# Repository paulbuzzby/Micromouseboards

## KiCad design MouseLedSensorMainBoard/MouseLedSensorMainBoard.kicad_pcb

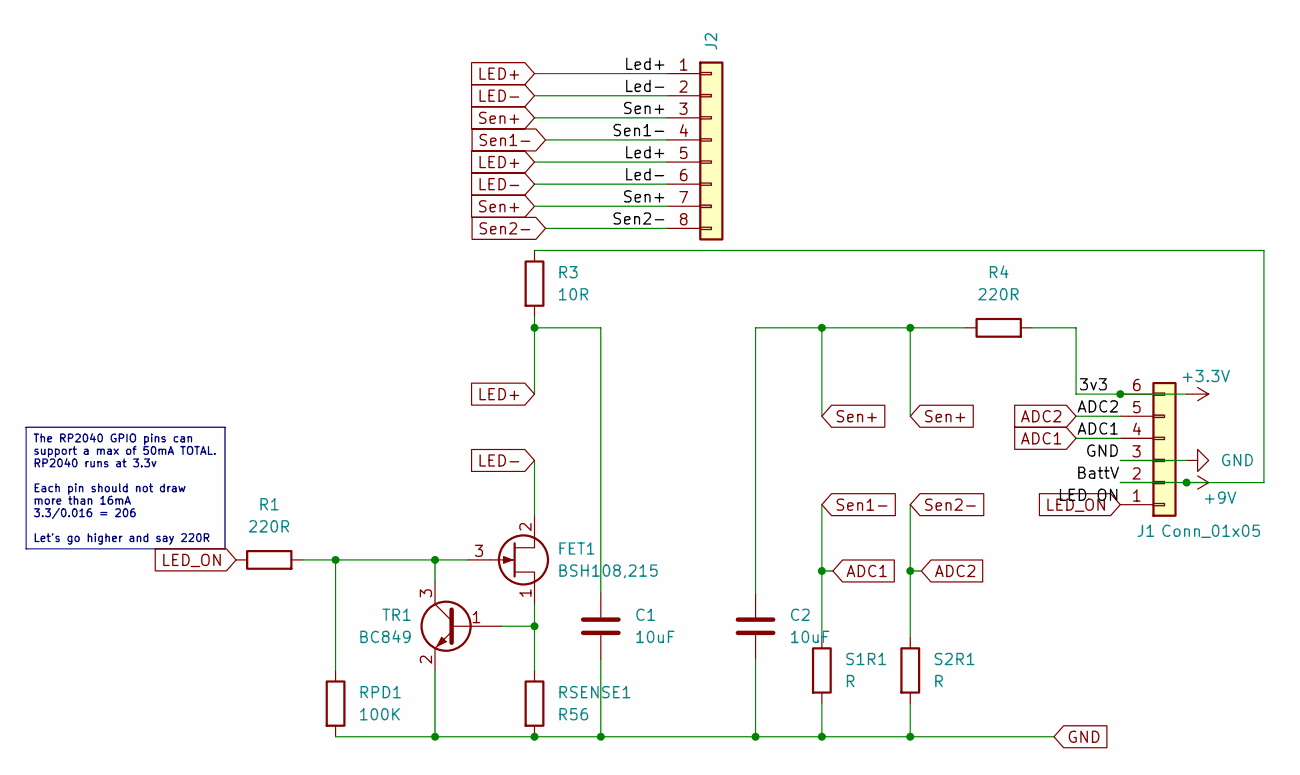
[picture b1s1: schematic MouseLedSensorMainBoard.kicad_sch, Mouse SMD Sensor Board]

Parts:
C1, C2: 10uF; C_0805_2012Metric_Pad1.18x1.45mm_HandSolder
FET1: BSH108,215; SOT-23
J1: Conn_01x05; PinHeader_1x06_P2.54mm_Vertical
J2: Conn_01x08; PinHeader_1x08_P2.54mm_Vertical
R1, R4: 220R; R_0805_2012Metric_Pad1.20x1.40mm_HandSolder
R3: 10R; R_0805_2012Metric_Pad1.20x1.40mm_HandSolder
RPD1: 100K; R_0805_2012Metric_Pad1.20x1.40mm_HandSolder
RSENSE1: R56; R_0805_2012Metric_Pad1.20x1.40mm_HandSolder
S1R1, S2R1: R; R_0805_2012Metric_Pad1.20x1.40mm_HandSolder
TR1: BC849; SOT-23

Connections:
+3.3V: J1.6, R4.2
+9V: J1.2, R3.1
ADC1: J1.4, J2.4, S1R1.1
ADC2: J1.5, J2.8, S2R1.1
GND: C1.2, C2.2, J1.3, RPD1.2, RSENSE1.2, S1R1.2, S2R1.2, TR1.2 (E)
LED+: C1.1, J2.1, J2.5, R3.2
LED-: FET1.2 (D), J2.2, J2.6
LED_ON: J1.1, R1.1
unnamed: FET1.3 (G), R1.2, RPD1.1, TR1.3 (C)
unnamed: FET1.1 (S), RSENSE1.1, TR1.1 (B)
Sen+: C2.1, J2.3, J2.7, R4.1

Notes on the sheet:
The RP2040 GPIO pins can support a max of 50mA TOTAL. RP2040 runs at 3.3v Each pin should not draw more than 16mA 3.3/0.016 = 206 Let's go higher and say 220R

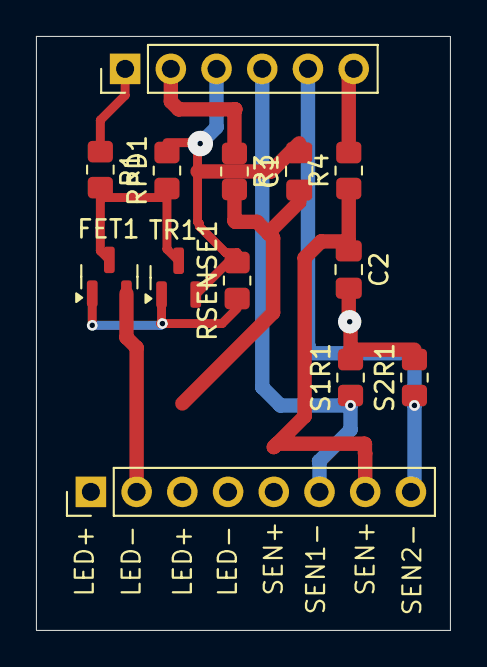
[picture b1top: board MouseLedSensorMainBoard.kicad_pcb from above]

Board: 2 copper layers, 23.0 x 33.0 mm, 13 parts (0 on the bottom side), 11 nets.

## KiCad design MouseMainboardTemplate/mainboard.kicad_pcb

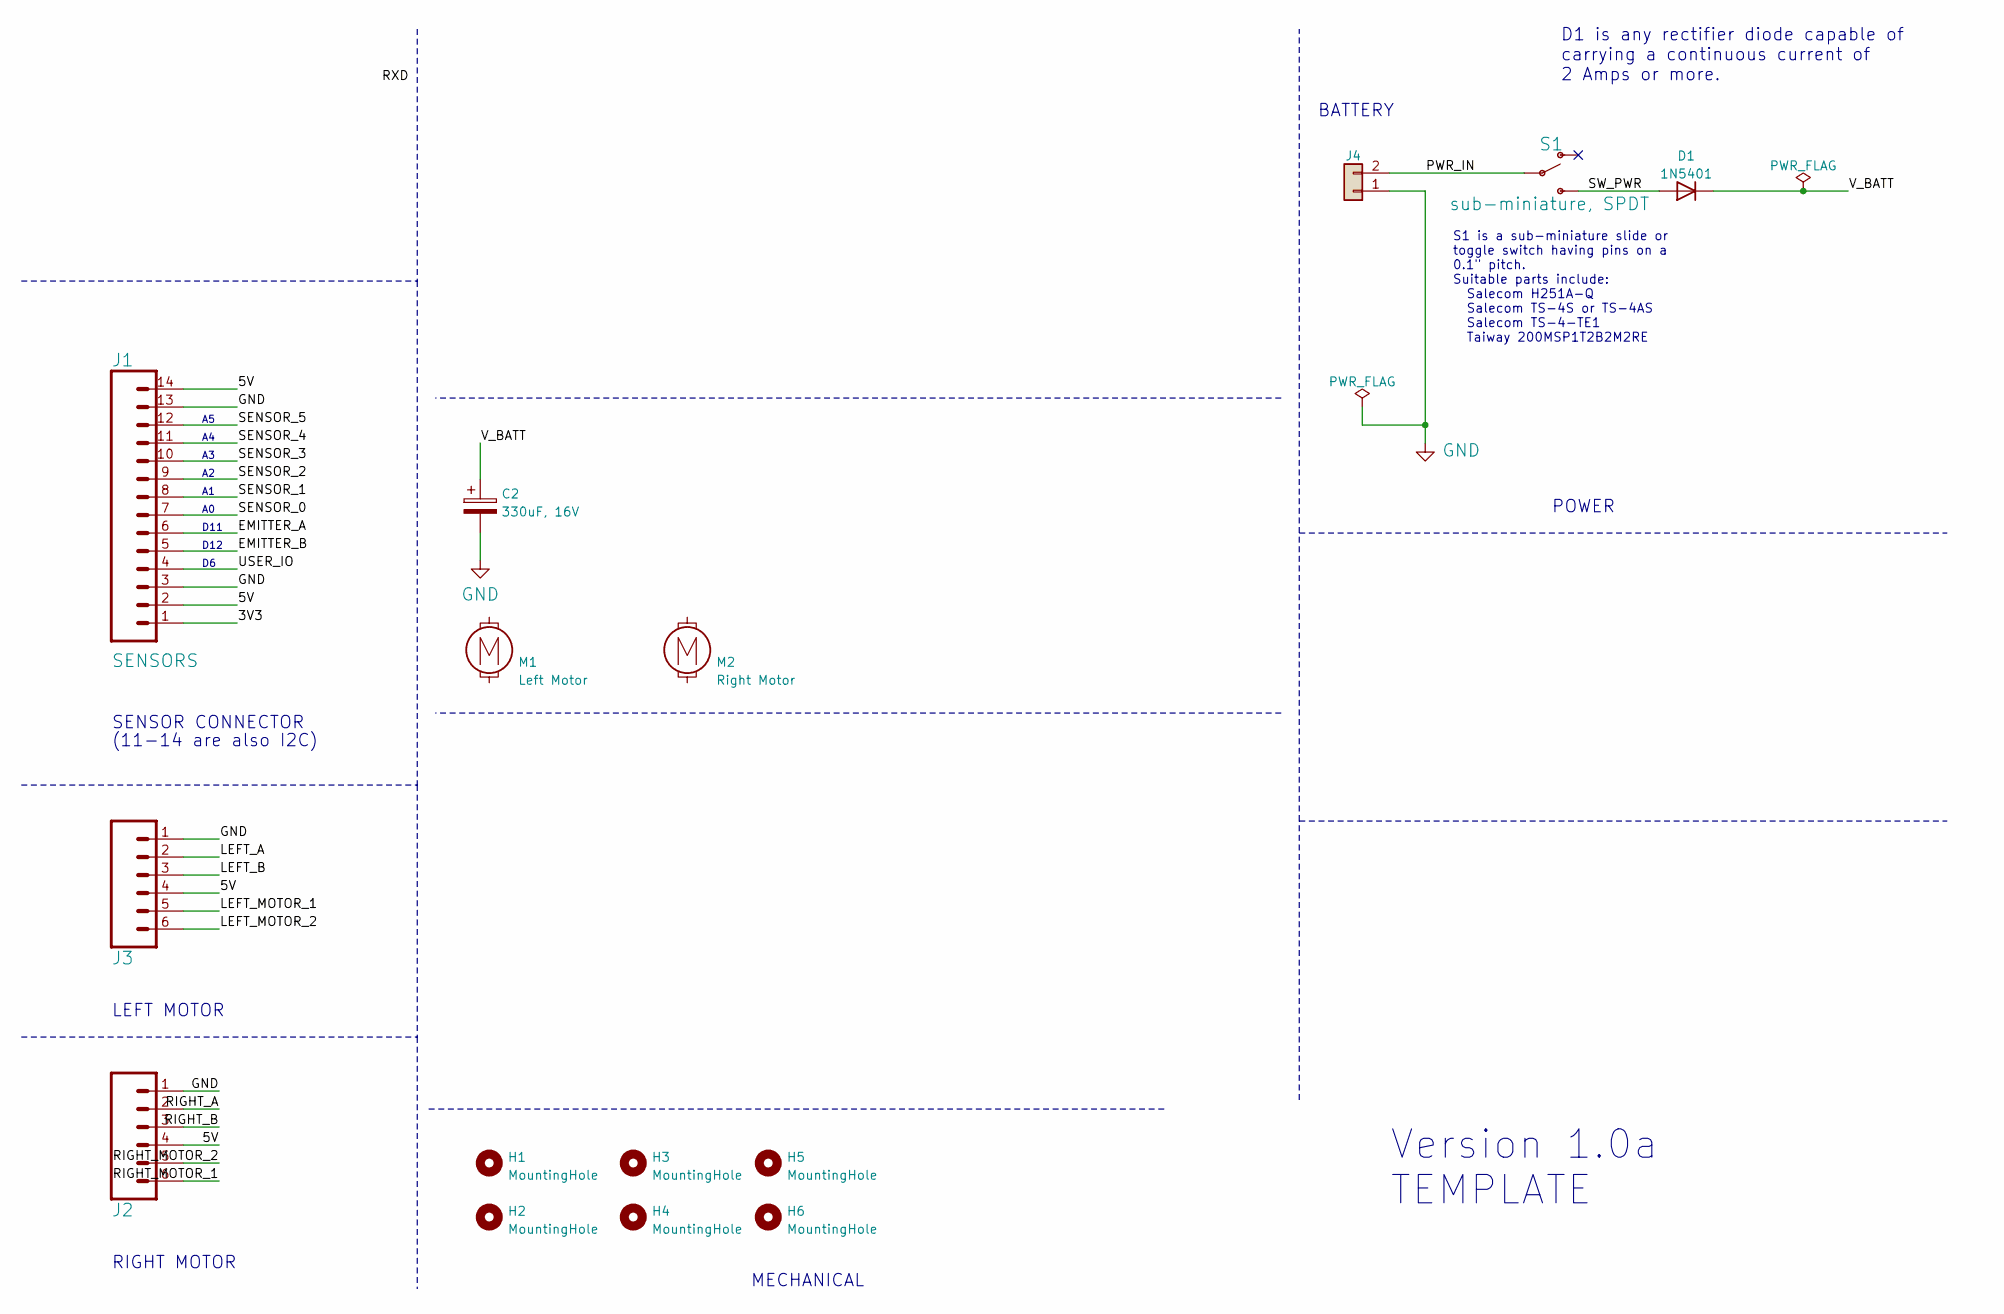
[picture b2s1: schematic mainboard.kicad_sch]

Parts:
C2: 330uF, 16V; CP_Radial_D8.0mm_P2.50mm
D1: 1N5401; D_DO-201AD_P15.24mm_Horizontal
H1, H2, H3, H4, H5, H6: MountingHole; MountingHole_3.2mm_M3_clearance
J1: SENSORS; 1X14_LOCK_LONGPADS
J2, J3: CONN_06SILK_FEMALE_PTH; 1X06_LOCK_LONGPADS
J4: POWER; Molex_KK-254_AE-6410-02A_1x02_P2.54mm_Vertical
M1: Left Motor; MINI-METAL-GEARMOTOR-WITH-BRACKET
M2: Right Motor; MINI-METAL-GEARMOTOR-WITH-BRACKET
S1: sub-miniature, SPDT; SW_MINI-SPDT-RTECH-78-0564

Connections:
/3V3: J1.1
/5V: J1.2, J1.14, J2.4, J3.4
/EMITTER_A: J1.6
/EMITTER_B: J1.5
/LEFT_A: J3.2
/LEFT_B: J3.3
/LEFT_MOTOR_1: J3.5
/LEFT_MOTOR_2: J3.6
/PWR_IN: J4.2, S1.2
/RIGHT_A: J2.2
/RIGHT_B: J2.3
/RIGHT_MOTOR_1: J2.6
/RIGHT_MOTOR_2: J2.5
/SENSOR_0: J1.7
/SENSOR_1: J1.8
/SENSOR_2: J1.9
/SENSOR_3: J1.10
/SENSOR_4: J1.11
/SENSOR_5: J1.12
/SW_PWR: D1.2 (A), S1.3 (S)
/USER_IO: J1.4
/V_BATT: C2.1, D1.1 (K)
GND: C2.2, J1.3, J1.13, J2.1, J3.1, J4.1

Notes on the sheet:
D1 is any rectifier diode capable of carrying a continuous current of 2 Amps or more.
POWER
S1 is a sub-miniature slide or toggle switch having pins on a 0.1" pitch. Suitable parts include: Salecom H251A-Q Salecom TS-4S or TS-4AS Salecom TS-4-TE1 Taiway 200MSP1T2B2M2RE
RIGHT MOTOR
SENSOR CONNECTOR
BATTERY
MECHANICAL
D11
Version 1.0a TEMPLATE
LEFT MOTOR
(11-14 are also I2C)
D12

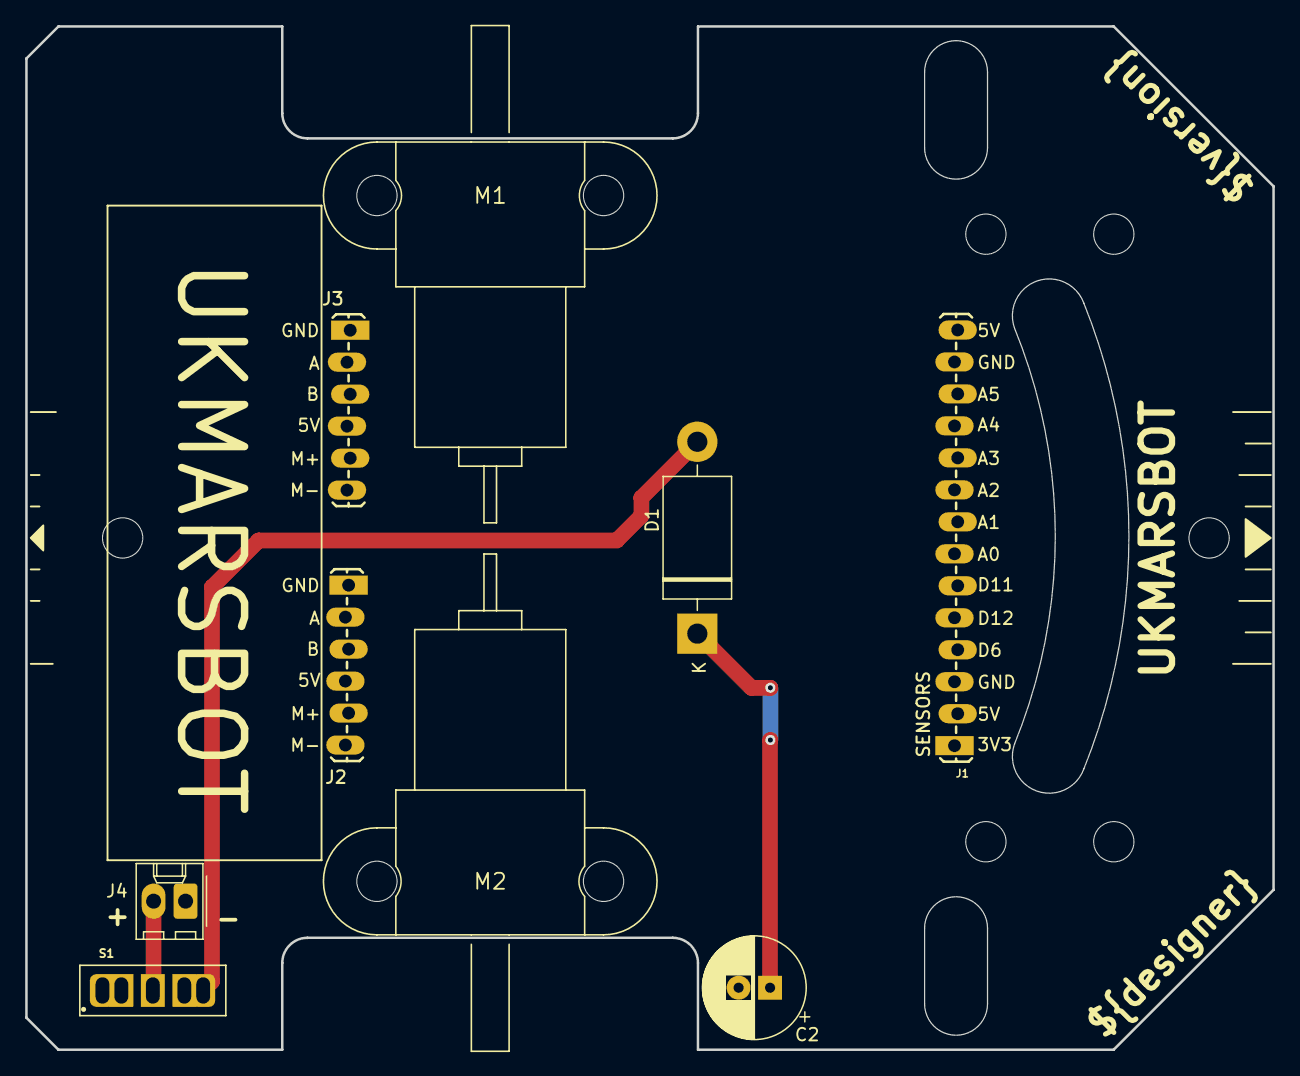
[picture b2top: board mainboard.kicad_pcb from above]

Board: 2 copper layers, 99.1 x 81.3 mm, 15 parts (0 on the bottom side), 5 nets.

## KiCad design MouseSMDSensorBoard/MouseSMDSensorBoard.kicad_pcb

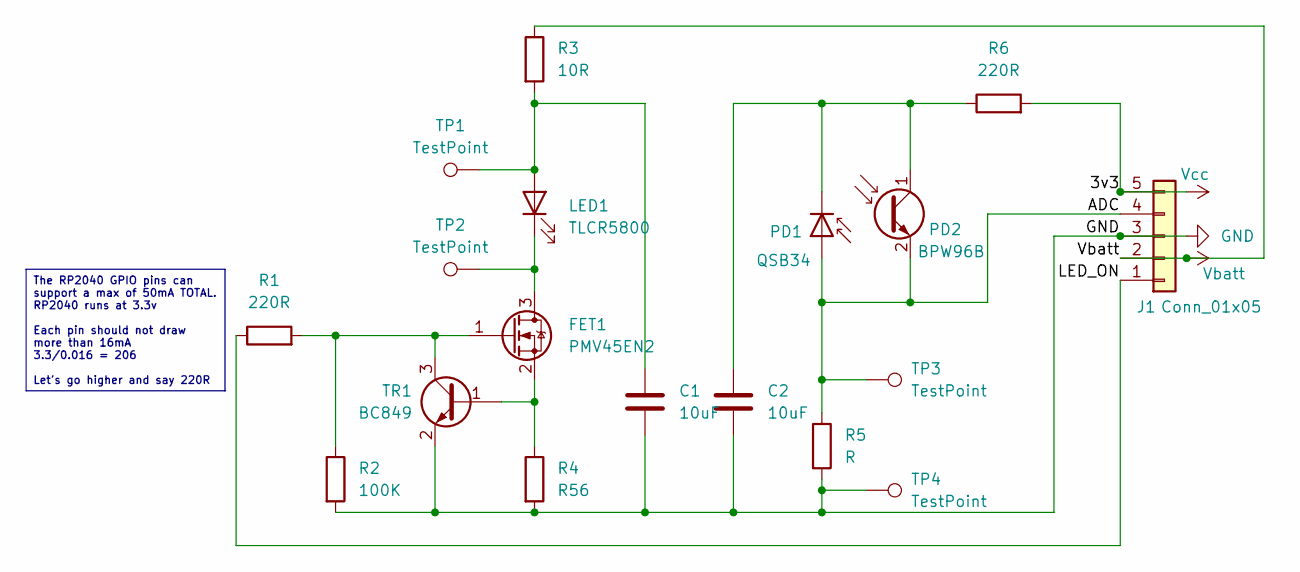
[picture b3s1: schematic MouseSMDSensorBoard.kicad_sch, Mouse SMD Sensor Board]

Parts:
C1, C2: 10uF; C_0805_2012Metric
FET1: PMV45EN2; SOT-23_Handsoldering
J1: Conn_01x05; PinHeader_1x05_P2.54mm_Vertical
LED1: TLCR5800; LED_D5.0mm
PD1: QSB34; PLCC_2L_Handsoldering
PD2: BPW96B; LED_D5.0mm
R1, R6: 220R; R_0805_2012Metric
R2: 100K; R_0805_2012Metric
R3: 10R; R_0805_2012Metric
R4: R56; R_0805_2012Metric
R5: R; R_0805_2012Metric
TP1, TP2, TP3, TP4: TestPoint; TestPoint_Pad_D1.5mm
TR1: BC849; SOT-23_Handsoldering

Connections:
/ADC: J1.4, PD1.2 (A), PD2.2 (E), R5.1, TP3.1
/LED_ON: J1.1, R1.1
GND: C1.2, C2.2, J1.3, R2.2, R4.2, R5.2, TP4.1, TR1.2 (E)
unnamed: FET1.3 (D), LED1.1 (K), TP2.1
unnamed: FET1.1 (G), R1.2, R2.1, TR1.3 (C)
unnamed: FET1.2 (S), R4.1, TR1.1 (B)
unnamed: C1.1, LED1.2 (A), R3.2, TP1.1
unnamed: C2.1, PD1.1 (K), PD2.1 (C), R6.1
Vbatt: J1.2, R3.1
Vcc: J1.5, R6.2

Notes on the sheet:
The RP2040 GPIO pins can support a max of 50mA TOTAL. RP2040 runs at 3.3v Each pin should not draw more than 16mA 3.3/0.016 = 206 Let's go higher and say 220R

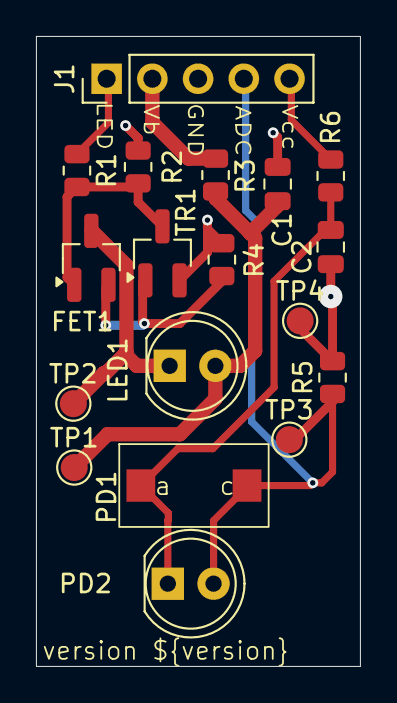
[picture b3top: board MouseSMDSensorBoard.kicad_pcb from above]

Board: 2 copper layers, 18.0 x 35.0 mm, 18 parts (0 on the bottom side), 10 nets.

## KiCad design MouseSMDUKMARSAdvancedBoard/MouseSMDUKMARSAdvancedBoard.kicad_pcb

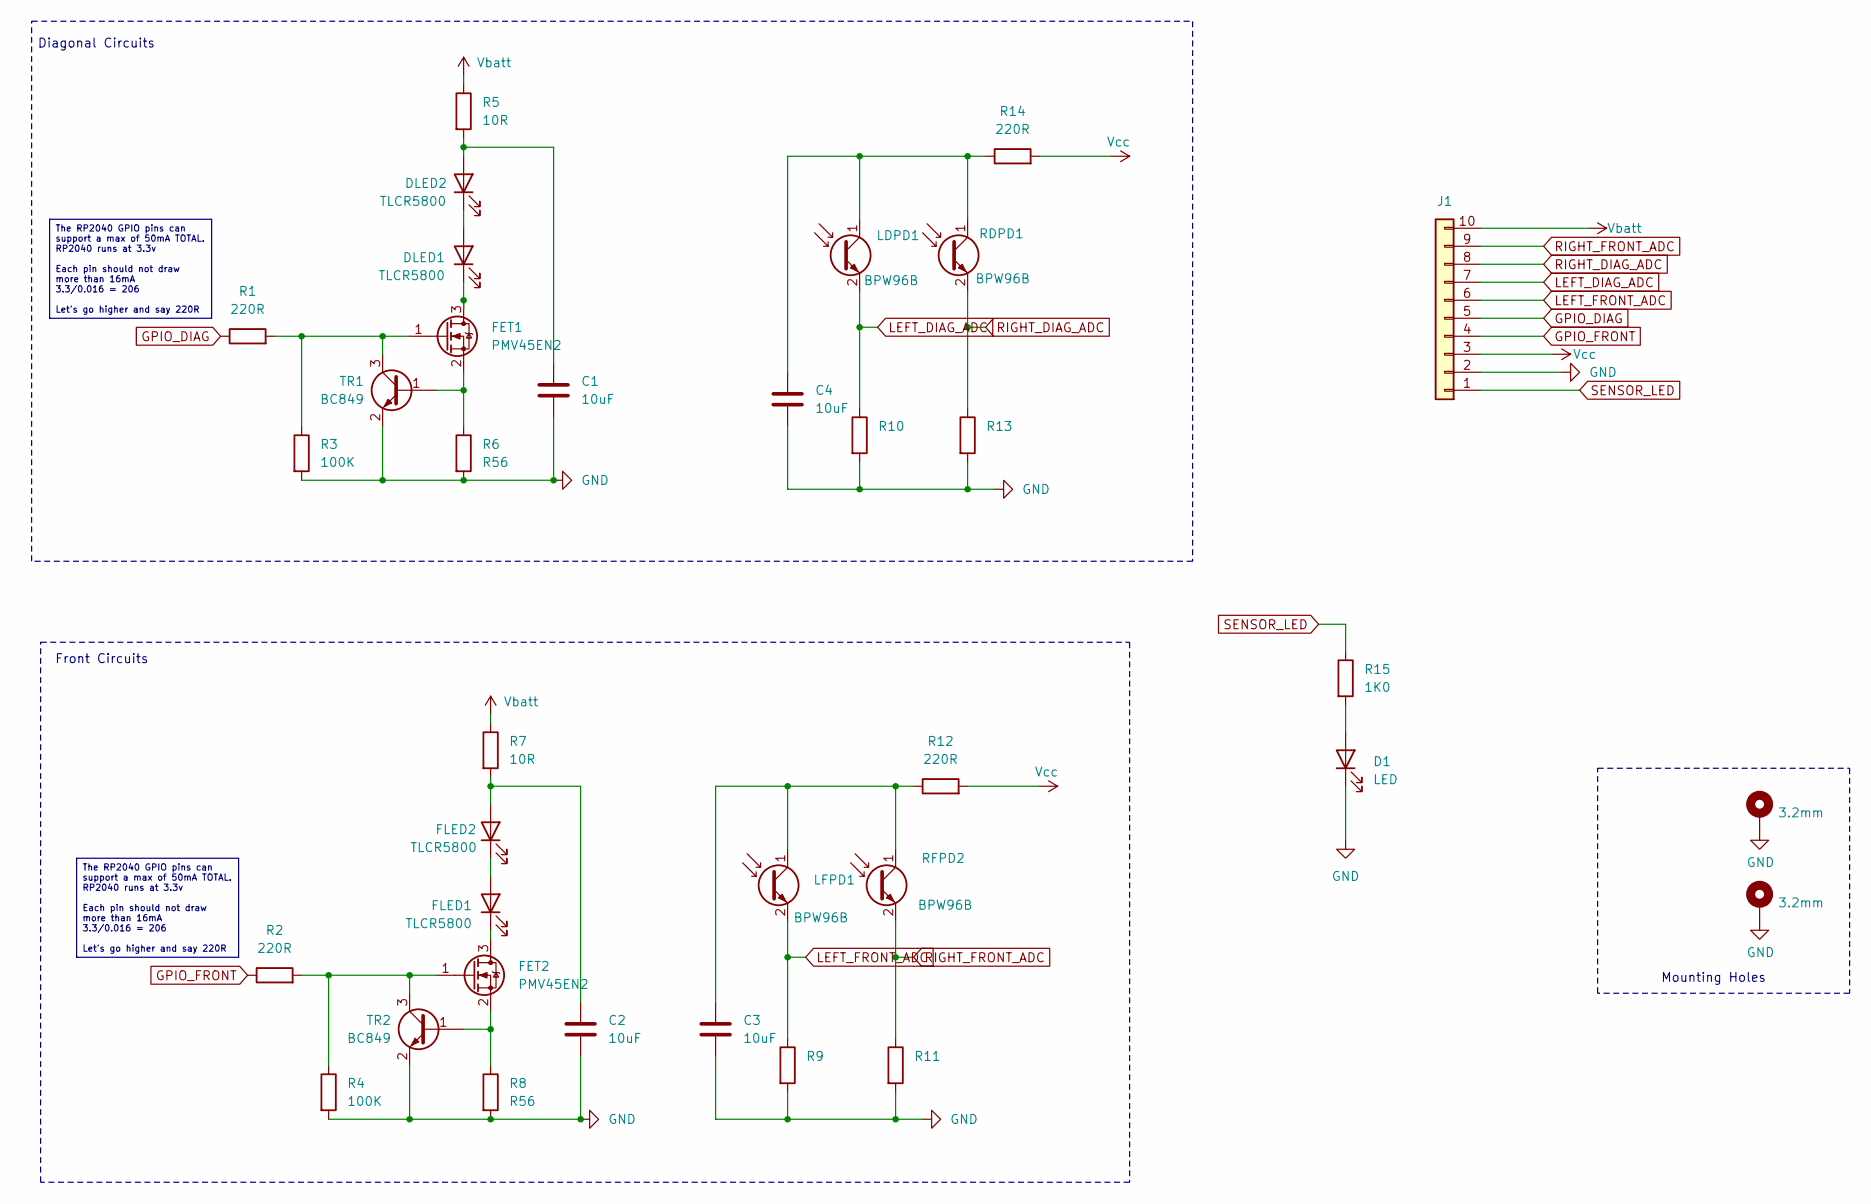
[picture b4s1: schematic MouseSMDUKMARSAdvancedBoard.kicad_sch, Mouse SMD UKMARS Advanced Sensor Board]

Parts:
C1, C2, C3, C4: 10uF; C_0805_2012Metric_Pad1.18x1.45mm_HandSolder
D1: LED; LED_1206_3216Metric_Pad1.42x1.75mm_HandSolder
DLED1, DLED2: TLCR5800; LED_D5.0mm_Horizontal_O1.27mm_Z3.0mm
FET1, FET2: PMV45EN2; SOT-23_Handsoldering
FLED1, FLED2: TLCR5800; LED_D5.0mm_Horizontal_O1.27mm_Z3.0mm
H1, H2: 3.2mm; MountingHole_3.2mm_M3_Pad
J1: Conn_01x10; PinHeader_1x10_P2.54mm_Vertical
LDPD1: BPW96B; LED_D5.0mm_Horizontal_O1.27mm_Z3.0mm
LFPD1: BPW96B; LED_D5.0mm_Horizontal_O1.27mm_Z3.0mm
R1, R2, R12, R14: 220R; R_0805_2012Metric_Pad1.20x1.40mm_HandSolder
R3, R4: 100K; R_0805_2012Metric_Pad1.20x1.40mm_HandSolder
R5, R7: 10R; R_0805_2012Metric_Pad1.20x1.40mm_HandSolder
R6, R8: R56; R_0805_2012Metric_Pad1.20x1.40mm_HandSolder
R9, R10, R11, R13: R; R_0805_2012Metric_Pad1.20x1.40mm_HandSolder
R15: 1K0; R_0805_2012Metric_Pad1.20x1.40mm_HandSolder
RDPD1: BPW96B; LED_D5.0mm_Horizontal_O1.27mm_Z3.0mm
RFPD2: BPW96B; LED_D5.0mm_Horizontal_O1.27mm_Z3.0mm
TR1, TR2: BC849; SOT-23_Handsoldering

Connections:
GND: C1.2, C2.2, C3.2, C4.2, D1.1 (K), H1.1, H2.1, J1.2, R3.2, R4.2, R6.2, R8.2, R9.2, R10.2, R11.2, R13.2, TR1.2 (E), TR2.2 (E)
GPIO_DIAG: J1.5, R1.1
GPIO_FRONT: J1.4, R2.1
LEFT_DIAG_ADC: J1.7, LDPD1.2 (E), R10.1
LEFT_FRONT_ADC: J1.6, LFPD1.2 (E), R9.1
unnamed: D1.2 (A), R15.2
unnamed: DLED1.2 (A), DLED2.1 (K)
unnamed: DLED1.1 (K), FET1.3 (D)
unnamed: C1.1, DLED2.2 (A), R5.2
unnamed: FET1.1 (G), R1.2, R3.1, TR1.3 (C)
unnamed: FET1.2 (S), R6.1, TR1.1 (B)
unnamed: FET2.3 (D), FLED1.1 (K)
unnamed: FET2.1 (G), R2.2, R4.1, TR2.3 (C)
unnamed: FET2.2 (S), R8.1, TR2.1 (B)
unnamed: FLED1.2 (A), FLED2.1 (K)
unnamed: C2.1, FLED2.2 (A), R7.2
unnamed: C4.1, LDPD1.1 (C), R14.1, RDPD1.1 (C)
unnamed: C3.1, LFPD1.1 (C), R12.1, RFPD2.1 (C)
RIGHT_DIAG_ADC: J1.8, R13.1, RDPD1.2 (E)
RIGHT_FRONT_ADC: J1.9, R11.1, RFPD2.2 (E)
SENSOR_LED: J1.1, R15.1
Vbatt: J1.10, R5.1, R7.1
Vcc: J1.3, R12.2, R14.2

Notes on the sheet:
The RP2040 GPIO pins can support a max of 50mA TOTAL. RP2040 runs at 3.3v Each pin should not draw more than 16mA 3.3/0.016 = 206 Let's go higher and say 220R
Diagonal Circuits
Mounting Holes
Front Circuits

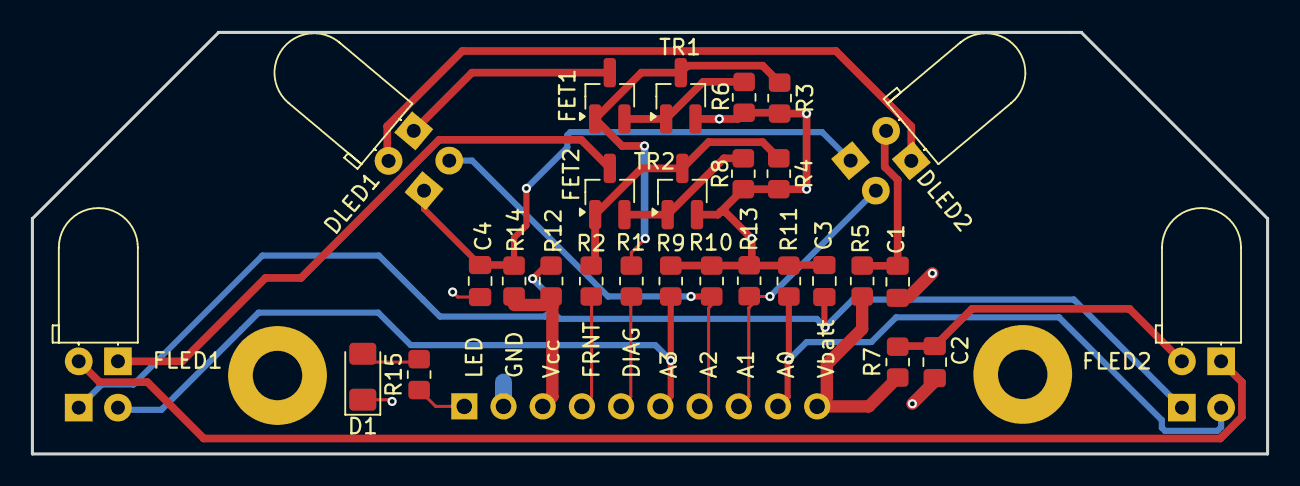
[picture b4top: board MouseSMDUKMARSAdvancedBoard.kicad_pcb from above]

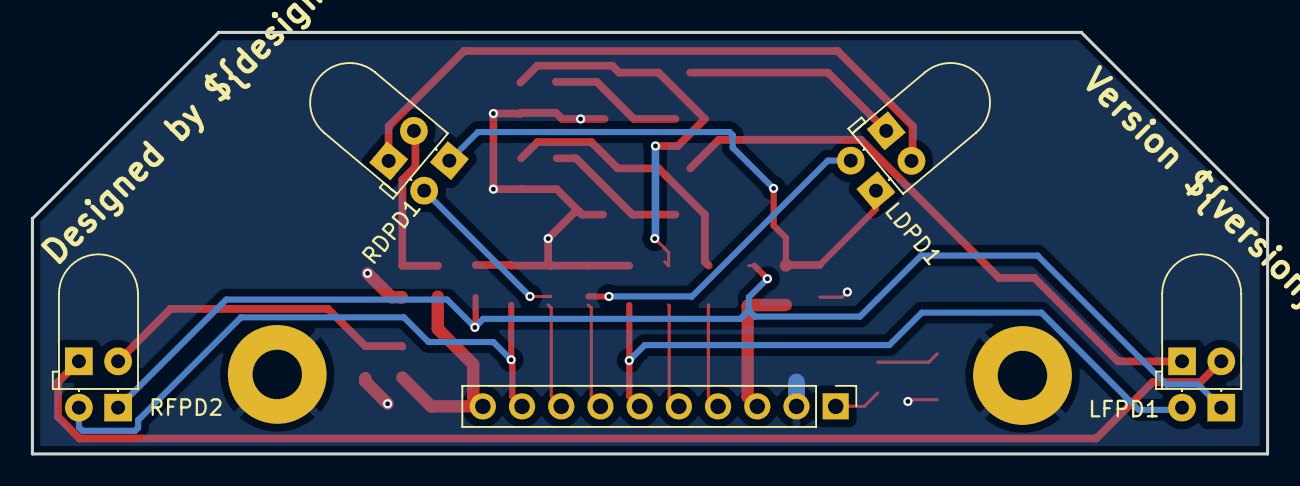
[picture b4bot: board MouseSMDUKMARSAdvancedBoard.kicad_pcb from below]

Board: 2 copper layers, 80.0 x 27.3 mm, 35 parts (5 on the bottom side), 23 nets.

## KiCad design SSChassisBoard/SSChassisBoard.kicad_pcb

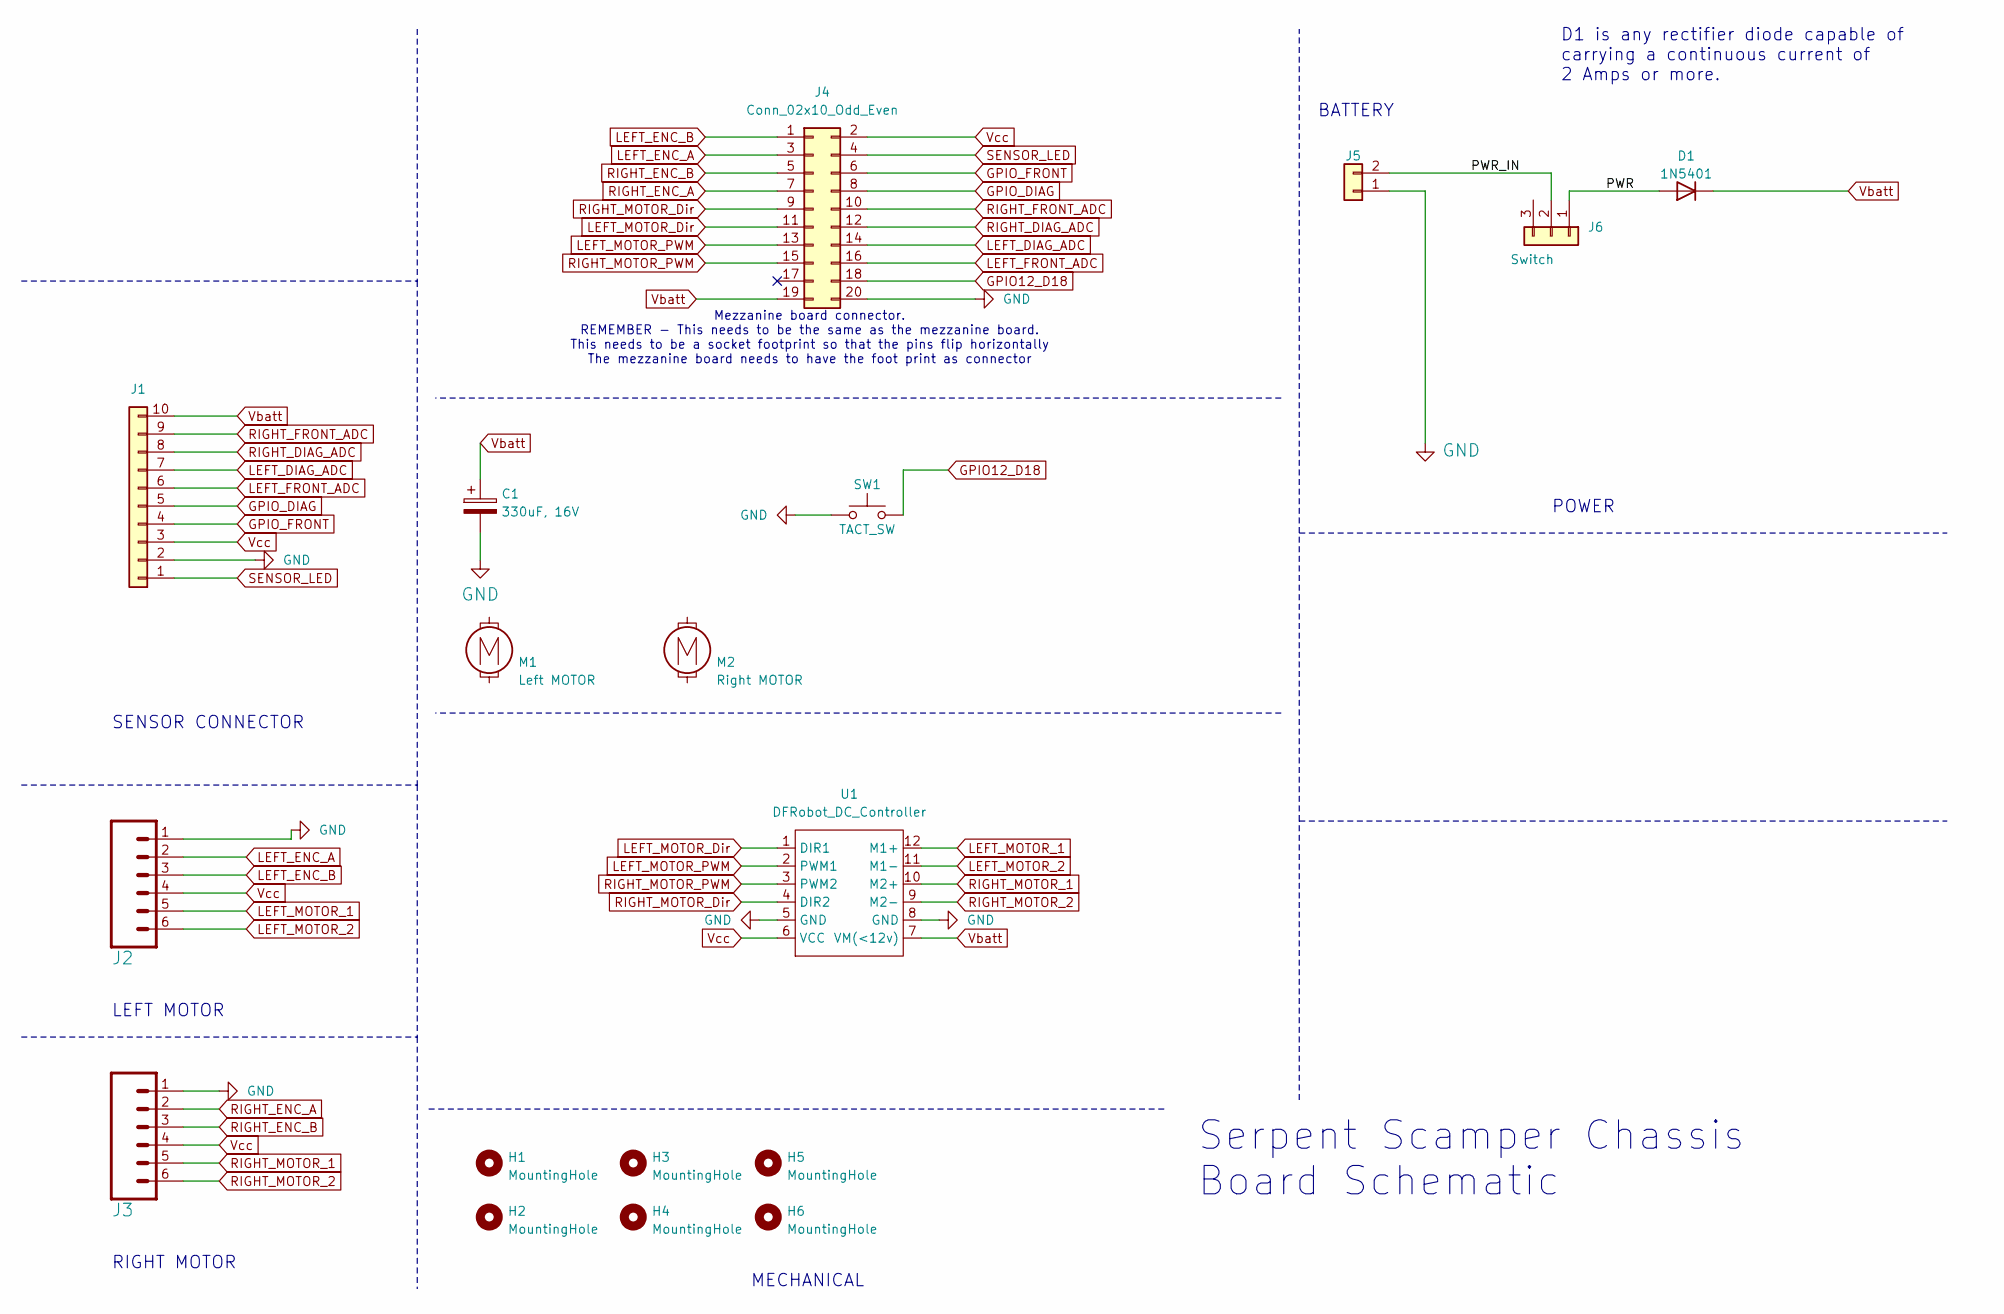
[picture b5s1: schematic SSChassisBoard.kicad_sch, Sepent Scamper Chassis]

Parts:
C1: 330uF, 16V; CP_Radial_D8.0mm_P2.50mm
D1: 1N5401; D_DO-201AD_P15.24mm_Horizontal
H1, H2, H3, H4, H5, H6: MountingHole; MountingHole_3.2mm_M3_clearance
J1: Conn_01x10; PinSocket_1x10_P2.54mm_Vertical
J2, J3: CONN_06SILK_FEMALE_PTH; 1X06_LOCK_LONGPADS
J4: Conn_02x10_Odd_Even; PinSocket_2x10_P2.54mm_Vertical
J5: POWER; Molex_KK-254_AE-6410-02A_1x02_P2.54mm_Vertical
J6: Switch; PinHeader_1x03_P2.54mm_Vertical
M1: Left MOTOR; MINI-METAL-GEARMOTOR-WITH-BRACKET_Alt
M2: Right MOTOR; MINI-METAL-GEARMOTOR-WITH-BRACKET
SW1: TACT_SW; SW_PUSH_6mm
U1: DFRobot_DC_Controller

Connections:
/PWR: D1.2 (A), J6.1
/PWR_IN: J5.2, J6.2
GND: C1.2, J1.2, J2.1, J3.1, J4.20, J5.1, SW1.1 (A), U1.5 (GND), U1.8 (GND)
GPIO12_D18: J4.18, SW1.2 (B)
GPIO_DIAG: J1.5, J4.8
GPIO_FRONT: J1.4, J4.6
LEFT_DIAG_ADC: J1.7, J4.14
LEFT_ENC_A: J2.2, J4.3
LEFT_ENC_B: J2.3, J4.1
LEFT_FRONT_ADC: J1.6, J4.16
LEFT_MOTOR_1: J2.5, U1.12 (M1+)
LEFT_MOTOR_2: J2.6, U1.11 (M1-)
LEFT_MOTOR_Dir: J4.11, U1.1 (DIR1)
LEFT_MOTOR_PWM: J4.13, U1.2 (PWM1)
RIGHT_DIAG_ADC: J1.8, J4.12
RIGHT_ENC_A: J3.2, J4.7
RIGHT_ENC_B: J3.3, J4.5
RIGHT_FRONT_ADC: J1.9, J4.10
RIGHT_MOTOR_1: J3.5, U1.10 (M2+)
RIGHT_MOTOR_2: J3.6, U1.9 (M2-)
RIGHT_MOTOR_Dir: J4.9, U1.4 (DIR2)
RIGHT_MOTOR_PWM: J4.15, U1.3 (PWM2)
SENSOR_LED: J1.1, J4.4
Vbatt: C1.1, D1.1 (K), J1.10, J4.19, U1.7 (VM(<12v))
Vcc: J1.3, J2.4, J3.4, J4.2, U1.6 (VCC)

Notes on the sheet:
D1 is any rectifier diode capable of carrying a continuous current of 2 Amps or more.
POWER
RIGHT MOTOR
SENSOR CONNECTOR
BATTERY
MECHANICAL
Mezzanine board connector. REMEMBER - This needs to be the same as the mezzanine board. This needs to be a socket footprint so that the pins flip horizontally The mezzanine board needs to have the foot print as connector
Serpent Scamper Chassis Board Schematic
LEFT MOTOR

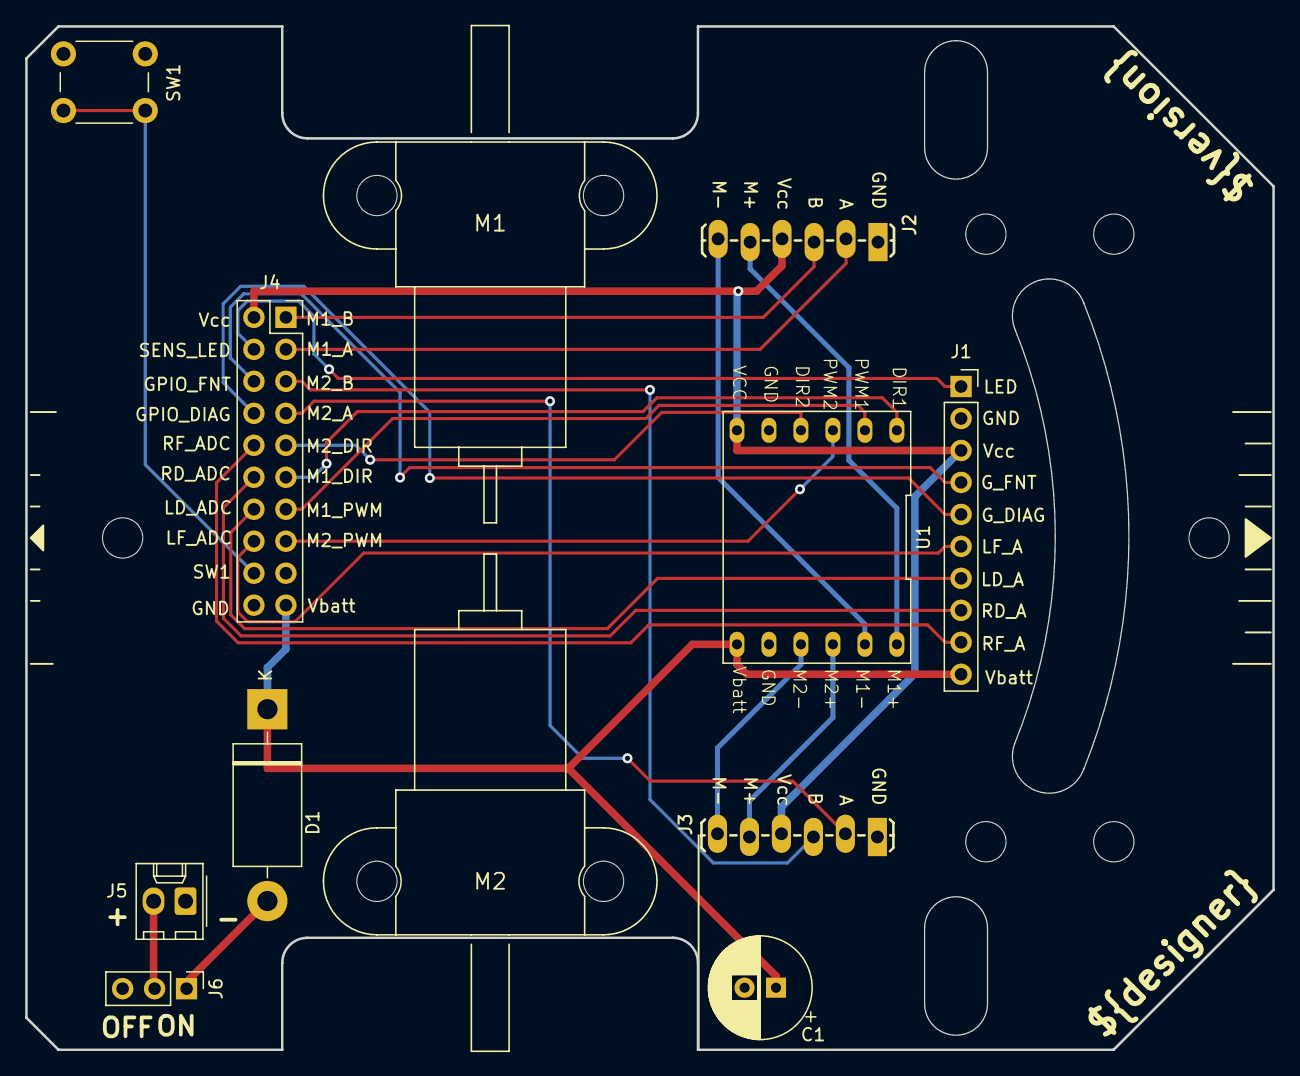
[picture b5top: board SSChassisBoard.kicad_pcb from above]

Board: 2 copper layers, 99.1 x 81.3 mm, 18 parts (0 on the bottom side), 25 nets.
